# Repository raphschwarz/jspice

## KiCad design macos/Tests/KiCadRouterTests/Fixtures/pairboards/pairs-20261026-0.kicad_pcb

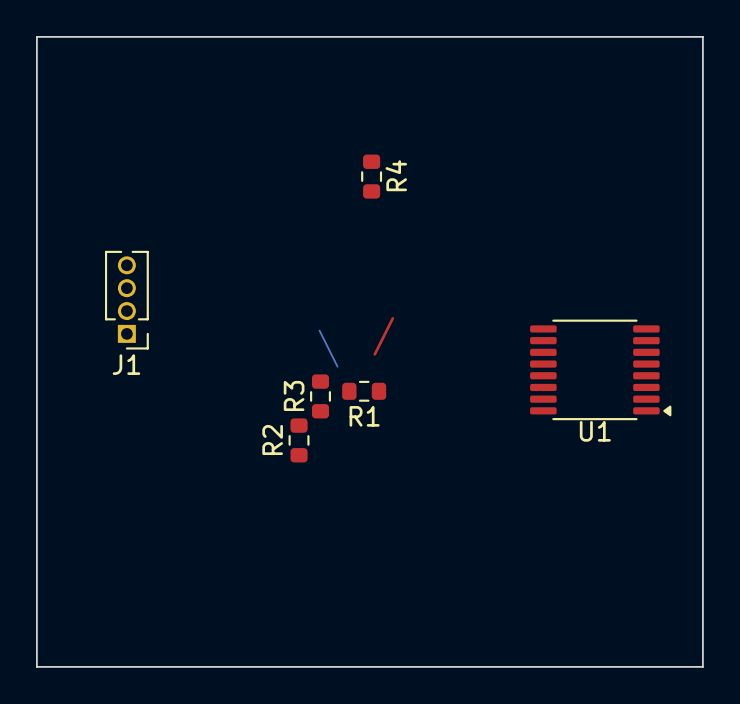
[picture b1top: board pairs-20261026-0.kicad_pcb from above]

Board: 2 copper layers, 37.0 x 35.0 mm, 6 parts (0 on the bottom side), 7 nets.

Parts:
J1: PinHeader_1x04_P1.27mm_Vertical
R1, R2, R3, R4: R_0603_1608Metric
U1: TSSOP-16_4.4x5mm_P0.65mm

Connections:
CLK_N: J1.2, U1.2
CLK_P: J1.1, U1.1
GND: R1.1, R1.2, R2.2, R3.1, U1.5
LVDS0_N: J1.4, U1.4
LVDS0_P: J1.3, U1.3
SIG1: R2.1, R4.2, U1.6, U1.10, U1.16
VCC: R3.2, R4.1, U1.7, U1.8, U1.9, U1.11, U1.12, U1.15
